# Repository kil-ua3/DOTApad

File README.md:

This is my DOTApad for playing Dota 2

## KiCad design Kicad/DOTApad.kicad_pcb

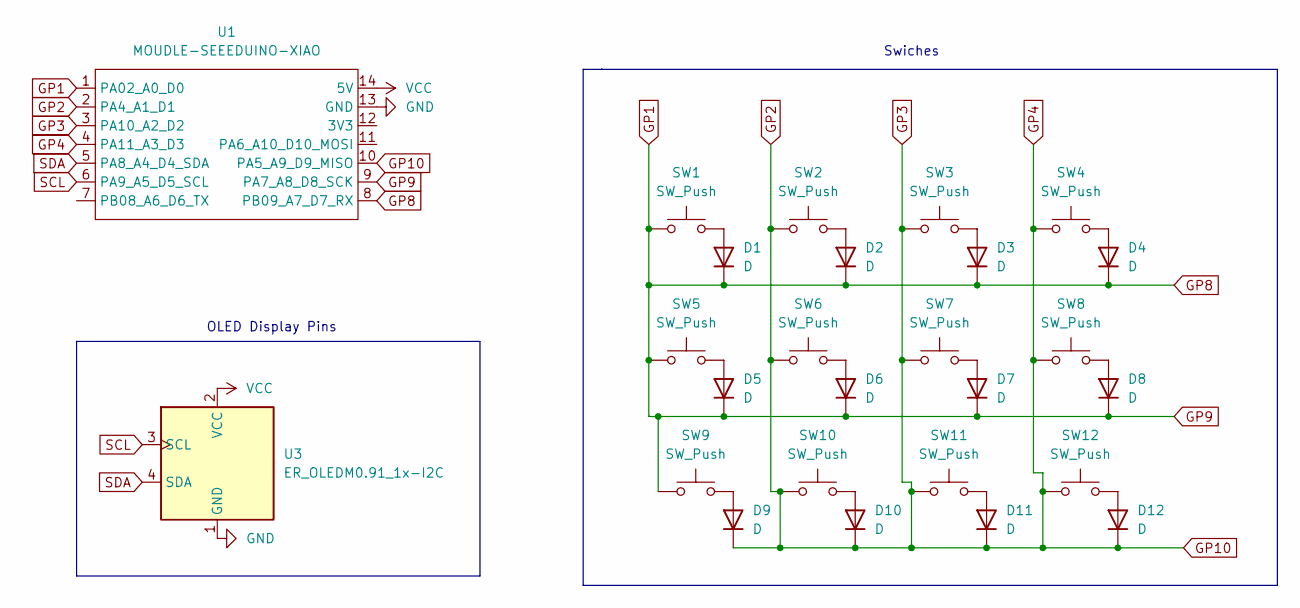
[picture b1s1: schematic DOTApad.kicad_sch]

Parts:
D1, D2, D3, D4, D5, D6, D7, D8, D9, D10, D11, D12: D; D_DO-35_SOD27_P7.62mm_Horizontal
SW1, SW2, SW3, SW4, SW5, SW6, SW7, SW8, SW9, SW10, SW11, SW12: SW_Push; SW_Cherry_MX_1.00u_PCB
U1: MOUDLE-SEEEDUINO-XIAO; MCU_Seeed_ESP32C3
U3: ER_OLEDM0.91_1x-I2C

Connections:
GND: U1.13 (GND), U3.1 (GND)
GP1: D1.1 (K), D2.1 (K), D3.1 (K), D4.1 (K), D5.1 (K), D6.1 (K), D7.1 (K), D8.1 (K), SW1.1, SW5.1, SW9.1, U1.1 (PA02_A0_D0), U1.8 (PB09_A7_D7_RX), U1.9 (PA7_A8_D8_SCK)
GP10: D9.1 (K), D10.1 (K), D11.1 (K), D12.1 (K), SW2.1, SW3.1, SW4.1, SW6.1, SW7.1, SW8.1, SW10.1, SW11.1, SW12.1, U1.2 (PA4_A1_D1), U1.3 (PA10_A2_D2), U1.4 (PA11_A3_D3), U1.10 (PA5_A9_D9_MISO)
unnamed: D1.2 (A), SW1.2
unnamed: D2.2 (A), SW2.2
unnamed: D3.2 (A), SW3.2
unnamed: D4.2 (A), SW4.2
unnamed: D5.2 (A), SW5.2
unnamed: D6.2 (A), SW6.2
unnamed: D7.2 (A), SW7.2
unnamed: D8.2 (A), SW8.2
unnamed: D9.2 (A), SW9.2
unnamed: D10.2 (A), SW10.2
unnamed: D11.2 (A), SW11.2
unnamed: D12.2 (A), SW12.2
SCL: U1.6 (PA9_A5_D5_SCL), U3.3 (SCL)
SDA: U1.5 (PA8_A4_D4_SDA), U3.4 (SDA)
VCC: U1.14 (5V), U3.2 (VCC)

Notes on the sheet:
OLED Display Pins
Swiches

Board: 2 copper layers, 26 parts (0 on the bottom side), 18 nets, no tracks yet.
